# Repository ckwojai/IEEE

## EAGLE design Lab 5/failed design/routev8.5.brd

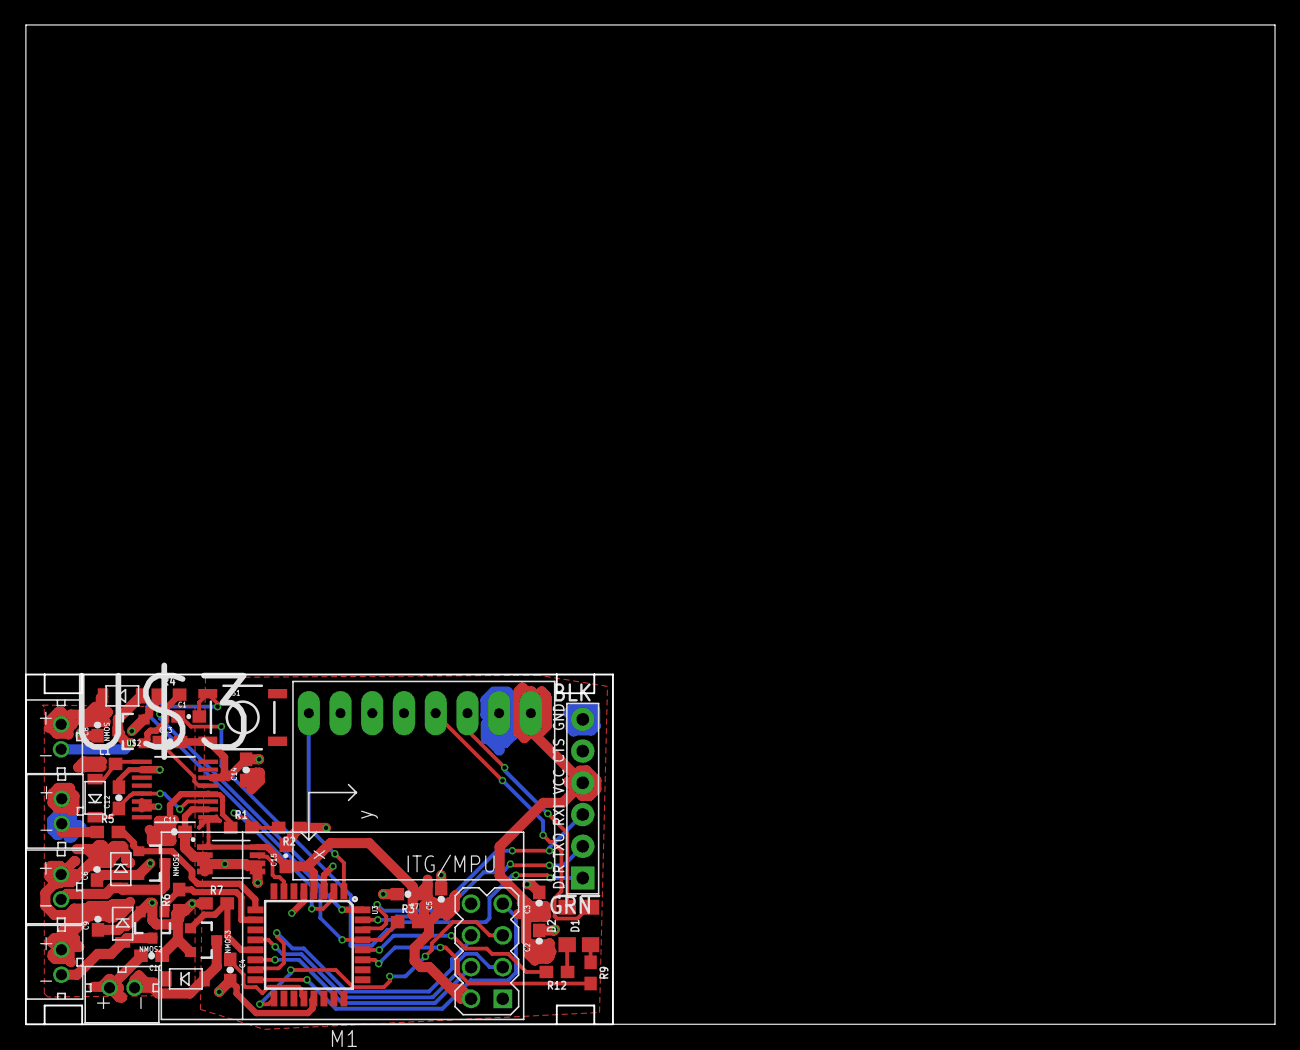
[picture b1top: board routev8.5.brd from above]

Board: 2 copper layers, 100.0 x 80.0 mm, 48 parts (0 on the bottom side), 33 nets.

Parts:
C1, C3, C4, C5, C7, C15: 100nF; 0603-CAP
C2: 10uF; 0603-CAP
C6, C8, C9, C10, C11, C12: 100uF; 0603-CAP
C13: 0.1uF; 0603-CAP
C14: 4.7uF; 0603-CAP
D1, D2: Yellow; LED-1206
DIODE, DIODE1, DIODE2, DIODE3, DIODE4: DB2W40300L; MINI2-F3-B
J2: FTDI_DEVICE; FTDI_DEVICE_SIDE
L1: 10uH; 0603
M1: WIRELESS-NRF24L01
MOTOR, MOTOR1, MOTOR2, MOTOR3: JST_CONNECTOR_FEMALE
NMOS, NMOS1, NMOS2, NMOS3: N-CHANNEL-MOSFET-IRLML6244TRPBF; SOT23-3
R1, R2: 2.2k; 0603
R3, R4, R5, R6, R7: 10k; 0603
R9, R12: 1k; 0603
S1: SWITCH-MOMENTARY-2SMD; TACTILE-SWITCH-SMD
U2: GY-521MPU6050; GY-521
U3: ATMEGA328P_TQFP; TQFP32-08
U$1: JST_CONNECTOR_FEMALE
U$2: MAX1672'MAX1672'; 21-0055H_16
U$3: LTC6930CMS8-8.19LTC6930CMS8-8.19; SOP65P490X110-8N

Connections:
BATTERY+: C6.2, C8.2, C9.2, C10.2, C11.1, DIODE.NEG, DIODE1.NEG, DIODE2.NEG, DIODE3.NEG, L1.1, MOTOR.+, MOTOR1.+, MOTOR2.+, MOTOR3.+, R1.1, U$1.+, U$2.12
FTDI-RX: J2.P$3, U3.30
FTDI-TX: J2.P$2, U3.31
GND: C2.2, C3.2, C4.2, C5.2, C6.1, C7.2, C8.1, C9.1, C10.1, C11.2, C12.2, C13.2, C14.2, C15.2, J2.P$6, M1.1, NMOS.2, NMOS1.2, NMOS2.2, NMOS3.2, R2.1, R4.1, R5.1, R6.1, R7.1, S1.3, U2.GND, U3.3, U3.5, U3.21, U$1.-, U$2.2, U$2.6, U$2.7, U$2.10, U$2.14, U$3.2, U$3.3, U$3.4, U$3.5, U$3.6
IMU-INT: U2.INT, U3.1
IMU-SCL: D2.C, U2.SCL
IMU-SDA: D1.C, U2.SDA
MEASURE_PIN: R1.2, R2.2, U3.2
MOTOR1: NMOS.1, R4.2, U3.32
MOTOR2: NMOS1.1, R5.2, U3.9
MOTOR3: NMOS2.1, R6.2, U3.10
MOTOR4: NMOS3.1, R7.2, U3.13
unnamed: DIODE4.POS, L1.2, U$2.1
unnamed: C4.1, U3.20
unnamed: D1.A, R9.1
unnamed: DIODE1.POS, MOTOR1.-, NMOS1.3
unnamed: DIODE2.POS, MOTOR2.-, NMOS2.3
unnamed: DIODE.POS, MOTOR.-, NMOS.3
unnamed: DIODE3.POS, MOTOR3.-, NMOS3.3
unnamed: R9.2, U3.27
unnamed: D2.A, R12.1
unnamed: R12.2, U3.28
unnamed: C1.1, J2.P$1
OSC1: U3.7, U$3.7
RESET: C1.2, R3.1, S1.1, U3.29
RF-CE: M1.3, U3.12
RF-CSN: M1.4, U3.14
RF-MISO: M1.7, U3.16
RF-MOSI: M1.6, U3.15
RF-SCK: M1.5, U3.17
VCC: C2.1, C3.1, C5.1, C7.1, C14.1, C15.1, J2.P$4, M1.2, R3.2, U2.VCC, U3.4, U3.18, U$2.9, U$3.1, U$3.8
VR-PS: C12.1, DIODE4.NEG, U$2.5, U$2.11
VR-REF: C13.1, U$2.13

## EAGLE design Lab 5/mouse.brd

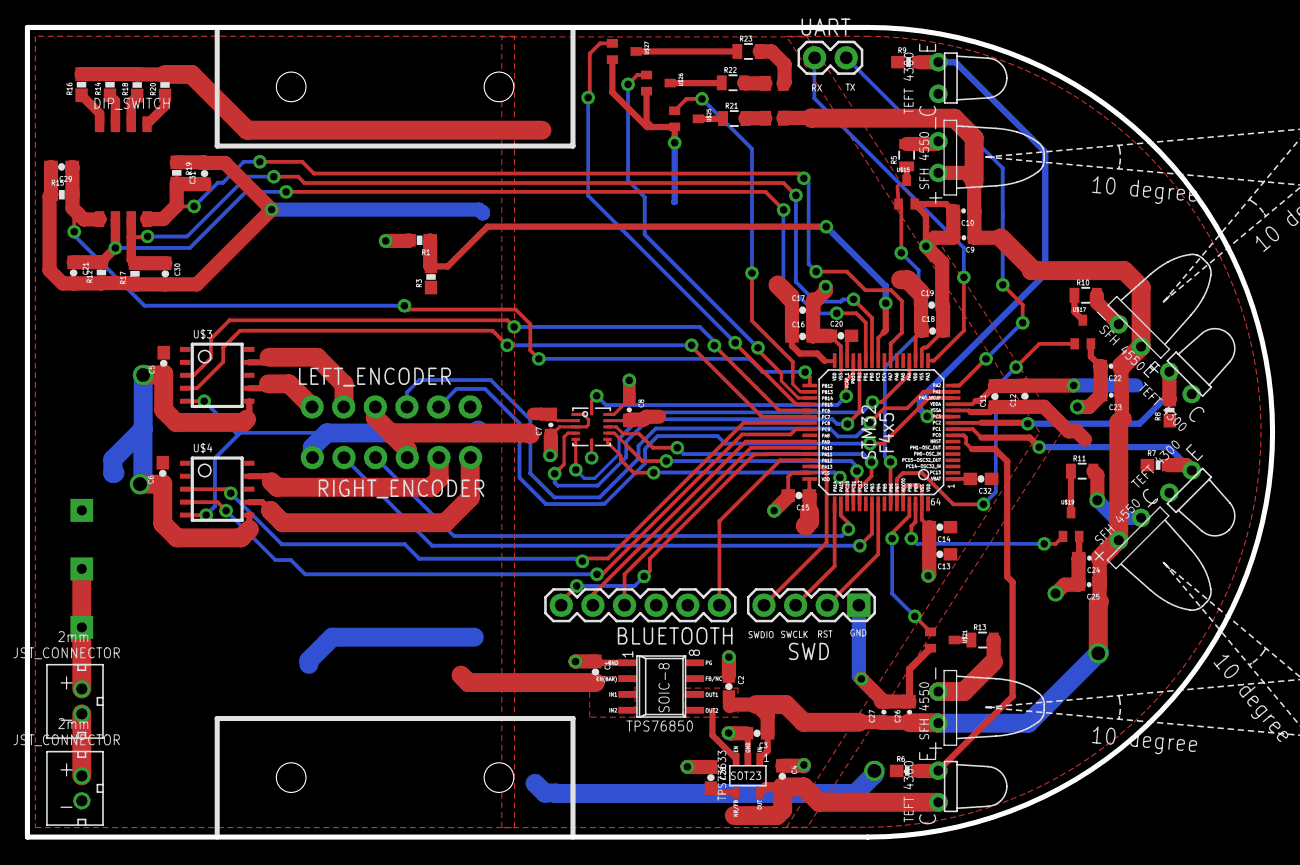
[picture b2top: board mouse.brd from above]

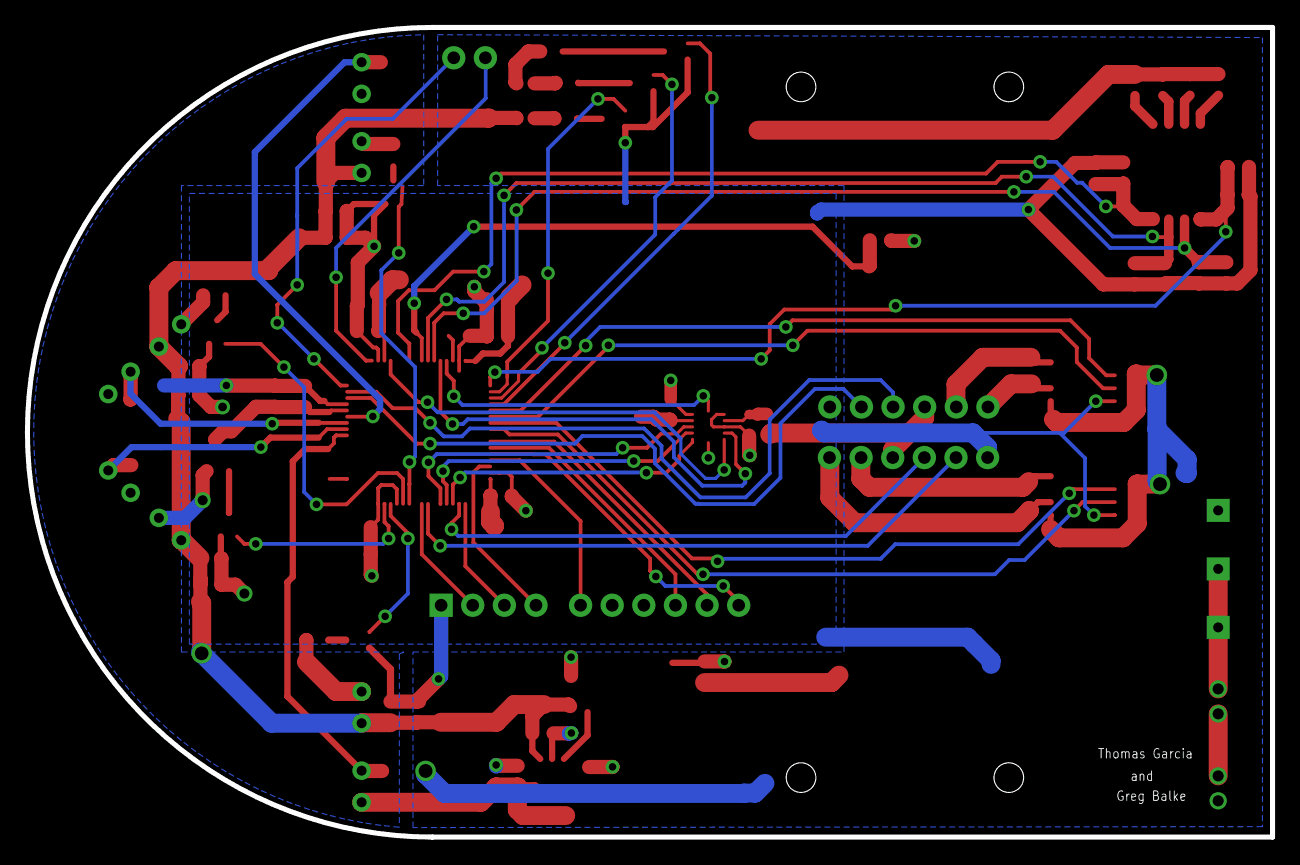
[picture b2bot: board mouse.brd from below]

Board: 2 copper layers, 100.0 x 65.0 mm, 94 parts (3 on the bottom side), 80 nets.

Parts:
BAT1, BAT2: JST_CONNECTOR_FEMALE
BLUETOOTH: 1X06
C1, C3, C7, C8, C9, C11, C13, C14, C15, C16, C17, C18, C21, C22, C24, C26, C29, C30, C31, C32: 100nF; 0603-CAP
C2, C4: 10uF; 0603-CAP
C5, C6, C12: 1uF; 0603-CAP
C10, C19, C20, C23, C25, C27: 4.7uF; 0603-CAP
C28: 10nF; 0603-CAP
DIP_SWITCH: 218_4LPSTR
LEFT_ENCODER: 1X06_NO_SILK
R1: 33k; 0603-RES
R3: 51k; 0603-RES
R5, R10, R11, R13: 36; 0805
R6, R7, R8, R9: 1.8k; 0603-RES
R12, R15, R17, R19: 10k; 0603-RES
R14, R16, R18, R20: 360; 0603-RES
R21, R22: 82; 0805
R23: 150; 0805
RIGHT_ENCODER: 1X06_NO_SILK
SWD: 1X04
U$1, U$2, U$9, U$13, U$14, U$29, U$30, U$31, U$32, U$33: SPLITTER
U$3, U$4: LB1930MCSMD; LB1930MC
U$5: XZMECBDDG45S; 4-PLCC
U$6: BMG160
U$7, U$16, U$18, U$34: EMITTER
U$8, U$10, U$11, U$12: RECEIVER
U$15, U$17, U$19, U$21, U$25, U$26, U$27: DMG1012UW
U$22: TPS76850(SOIC-8)
U$23: TPS73633(SOT-23)
U$24: STM32F411RE_LQFP64
U$28: 500SSP1S2M2QEA
UART: 1X02

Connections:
5V: C2.2, C3.1, C9.1, C10.1, C22.1, C23.1, C24.1, C25.1, C26.1, C27.1, U$5.VCC, U$7.+, U$16.+, U$18.+, U$22.OUT1, U$22.OUT2, U$23.EN, U$23.IN, U$34.+
AGND: C11.1, C12.1, R6.1, R7.1, R8.1, R9.1, U$9.1, U$24.VSSA
BAT: C1.2, C5.2, C6.2, R3.1, U$3.1, U$4.1, U$22.EN(BAR), U$22.IN1, U$22.IN2, U$28.1
BAT_DIVIDER: R1.1, R3.2, U$24.PC5
BLUE_GATE: U$24.PB13, U$25.GATE
BRX: BLUETOOTH.4, U$24.PA10
BTX: BLUETOOTH.5, U$24.PA9
BUTTON1: C29.1, DIP_SWITCH.OUT1, R15.2, U$24.PB12
BUTTON2: C21.1, DIP_SWITCH.OUT2, R12.2, U$24.PB1
BUTTON3: C30.1, DIP_SWITCH.OUT3, R17.2, U$24.PB0
BUTTON4: C31.1, DIP_SWITCH.OUT4, R19.2, U$24.PA7
CTS: BLUETOOTH.6, U$24.PA11
DGND: BLUETOOTH.3, C7.1, C8.1, C9.2, C10.2, C13.2, C14.2, C15.2, C16.2, C17.2, C18.2, C19.2, C20.1, C21.2, C22.2, C23.2, C24.2, C25.2, C26.2, C27.2, C29.2, C30.2, C31.2, LEFT_ENCODER.6, R12.1, R15.1, R17.1, R19.1, RIGHT_ENCODER.6, SWD.1, U$2.1, U$3.5, U$4.5, U$6.P$1, U$6.P$3, U$6.P$6, U$6.P$11, U$15.SOURCE, U$17.SOURCE, U$19.SOURCE, U$21.SOURCE, U$24.BOOT0, U$24.VSS_0, U$24.VSS_1, U$24.VSS_2, U$24.VSS_3, U$25.SOURCE, U$26.SOURCE, U$27.SOURCE
FRONT_LEFT_EMITTER: U$17.GATE, U$24.PB7
FRONT_LEFT_RECEIVER: R8.2, U$11.E, U$24.PC2
FRONT_RIGHT_EMITTER: U$19.GATE, U$24.PB9
FRONT_RIGHT_RECEIVER: R7.2, U$10.E, U$24.PC1
GND: BAT1.-, C1.1, C2.1, C3.2, C4.1, C28.1, R1.2, U$1.2, U$2.2, U$9.2, U$22.GND, U$23.GND
GREEN_GATE: U$24.PB14, U$26.GATE
GYRO_INT1: U$6.P$4, U$24.PB2
GYRO_INT2: U$6.P$12, U$24.PB10
LEFT_A: LEFT_ENCODER.4, U$24.PA1
LEFT_B: LEFT_ENCODER.5, U$24.PA0_WKUP
LEFT_BWD: U$3.3, U$24.PC6
LEFT_EMITTER: U$15.GATE, U$24.PB6
LEFT_FWD: U$3.4, U$24.PC7
LEFT_RECEIVER: R9.2, U$12.E, U$24.PC3
MGND: C5.1, C6.1, U$1.1, U$3.10, U$4.10
MISO: U$6.P$8, U$24.PC11
MOSI: U$6.P$9, U$24.PC12
unnamed: BAT1.+, BAT2.-
unnamed: RIGHT_ENCODER.2, U$4.7
unnamed: RIGHT_ENCODER.1, U$4.9
unnamed: LEFT_ENCODER.2, U$3.7
unnamed: LEFT_ENCODER.1, U$3.9
unnamed: R5.2, U$34.-
unnamed: BAT2.+, U$28.2, U$28.3
unnamed: C20.2, U$24.VCAP_1
unnamed: R5.1, U$15.DRAIN
unnamed: R10.2, U$7.-
unnamed: R10.1, U$17.DRAIN
unnamed: R11.2, U$16.-
unnamed: R21.2, U$5.BLUE
unnamed: R11.1, U$19.DRAIN
unnamed: R13.2, U$18.-
unnamed: R13.1, U$21.DRAIN
unnamed: C28.2, U$23.NR/FB
unnamed: C4.2, U$13.2, U$14.2, U$23.OUT
unnamed: C32.2, U$24.VBAT
unnamed: DIP_SWITCH.IN2, R14.1
unnamed: DIP_SWITCH.IN1, R16.1
unnamed: R22.2, U$5.GREEN
unnamed: DIP_SWITCH.IN3, R18.1
unnamed: R23.2, U$5.RED
unnamed: DIP_SWITCH.IN4, R20.1
unnamed: R22.1, U$26.DRAIN
unnamed: R21.1, U$25.DRAIN
unnamed: R23.1, U$27.DRAIN
unnamed: C8.2, U$6.P$10, U$32.2
unnamed: C7.2, U$6.P$2, U$31.2
RED_GATE: U$24.PB15, U$27.GATE
RIGHT_A: RIGHT_ENCODER.4, U$24.PA15
RIGHT_B: RIGHT_ENCODER.5, U$24.PB3
RIGHT_BWD: U$4.3, U$24.PC8
RIGHT_EMITTER: U$21.GATE, U$24.PB8
RIGHT_FWD: U$4.4, U$24.PC9
RIGHT_RECEIVER: R6.2, U$8.E, U$24.PC0
RST: SWD.2, U$24.PB4
RTS: BLUETOOTH.1, U$24.PA12
RX: U$24.PA3, UART.1
SCK: U$6.P$7, U$24.PC10
SS: U$6.P$5, U$24.PA4
SWCLK: SWD.3, U$24.PA14
SWDIO: SWD.4, U$24.PA13
TX: U$24.PA2, UART.2
VDD: BLUETOOTH.2, C13.1, C14.1, C32.1, LEFT_ENCODER.3, R14.2, R16.2, R18.2, R20.2, RIGHT_ENCODER.3, U$13.1, U$24.VDD_3, U$29.2, U$30.2, U$31.1, U$32.1, U$33.1
VDD15: C15.1, U$24.VDD_2, U$33.2
VDDA: C11.2, C12.2, U$8.C, U$10.C, U$11.C, U$12.C, U$14.1, U$24.VDDA
VDD_0: C18.1, C19.1, U$24.VDD_0, U$30.1
VDD_1: C16.1, C17.1, U$24.VDD_1, U$29.1

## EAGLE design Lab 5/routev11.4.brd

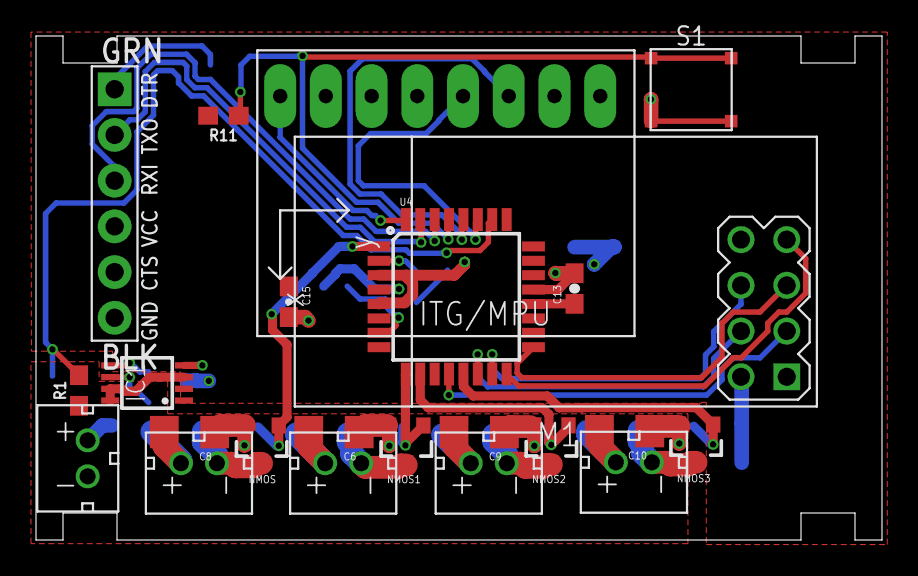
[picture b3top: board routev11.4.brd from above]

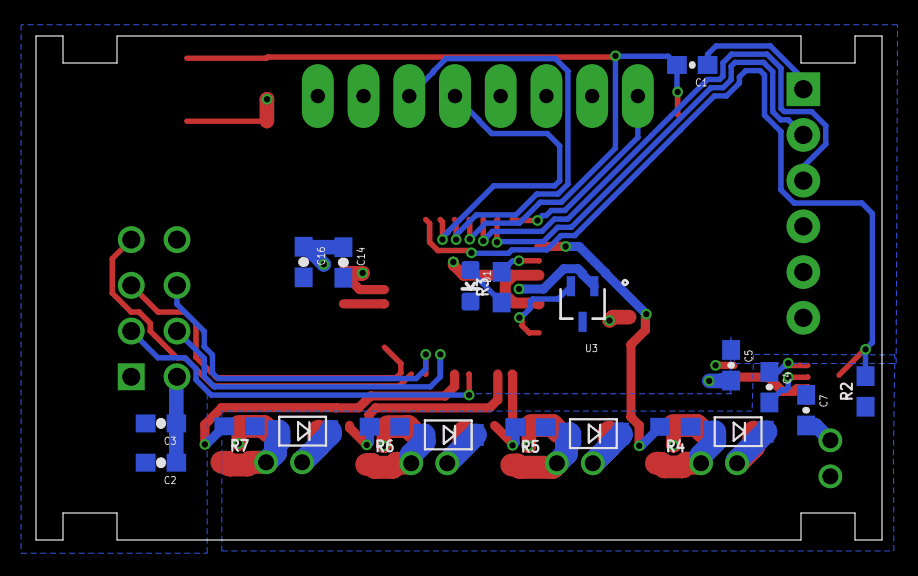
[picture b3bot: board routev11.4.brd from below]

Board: 2 copper layers, 47.0 x 28.0 mm, 43 parts (20 on the bottom side), 30 nets.

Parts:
C1, C3, C13, C14, C15, C16: 100nF; 0603-CAP
C2, C5, C7: 10uF; 0603-CAP
C4: 1uF; 0603-CAP
C6, C8, C9, C10: 100uF; 1206
D1: BLUE; LED-0603
DIODE, DIODE1, DIODE2, DIODE3: DB2W40300L; MINI2-F3-B
IC1: MCP1253-ADJ; MSOP8
J1: FTDI_DEVICE; FTDI_DEVICE_SIDE
M1: WIRELESS-NRF24L01
MOTOR1, MOTOR2, MOTOR3, MOTOR4: JST_CONNECTOR_FEMALE
NMOS, NMOS1, NMOS2, NMOS3: N-CHANNEL-MOSFET-IRLML6244TRPBF; SOT23-3
R1, R2, R3: 2.2k; 0603
R4, R5, R6, R7, R11: 10k; 0603
S1: TL3315NF100Q
U2: GY-521MPU6050; GY-521
U3: MAX7375AXR805-T; 21-0075D
U4: ATMEGA328P_TQFP; TQFP32-08
U$1: JST_CONNECTOR_FEMALE

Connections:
BATTERY+: C6.2, C7.2, C8.2, C9.2, C10.2, DIODE.NEG, DIODE1.NEG, DIODE2.NEG, DIODE3.NEG, IC1.3, IC1.7, IC1.8, MOTOR1.+, MOTOR2.+, MOTOR3.+, MOTOR4.+, R1.1, U$1.+
FTDI-RX: J1.P$3, U4.30
FTDI-TX: J1.P$2, U4.31
GND: C2.2, C3.2, C5.1, C6.1, C7.1, C8.1, C9.1, C10.1, C13.2, C14.2, C15.2, C16.2, D1.C, IC1.4, J1.P$6, M1.1, NMOS.2, NMOS1.2, NMOS2.2, NMOS3.2, R2.1, R4.1, R5.1, R6.1, R7.1, S1.3, S1.4, U2.GND, U3.3, U4.3, U4.5, U4.21, U$1.-
IMU-INT: U2.INT, U4.32
IMU-SCL: U2.SCL, U4.28
IMU-SDA: U2.SDA, U4.27
MEASURE_PIN: R1.2, R2.2, U4.26
MOTOR1: NMOS.1, R4.2, U4.1
MOTOR2: NMOS1.1, R5.2, U4.9
MOTOR3: NMOS2.1, R6.2, U4.10
MOTOR4: NMOS3.1, R7.2, U4.13
unnamed: R3.2, U4.2
unnamed: C1.1, J1.P$1
unnamed: DIODE1.POS, MOTOR2.-, NMOS1.3
unnamed: DIODE2.POS, MOTOR3.-, NMOS2.3
unnamed: DIODE.POS, MOTOR1.-, NMOS.3
unnamed: DIODE3.POS, MOTOR4.-, NMOS3.3
unnamed: C4.1, IC1.5
unnamed: C4.2, IC1.6
unnamed: D1.A, R3.1
unnamed: C13.1, U4.20
OSC1: U3.2, U4.7
RESET: C1.2, R11.1, S1.1, S1.2, U4.29
RF-CE: M1.3, U4.12
RF-CSN: M1.4, U4.14
RF-MISO: M1.7, U4.16
RF-MOSI: M1.6, U4.15
RF-SCK: M1.5, U4.17
VCC: C2.1, C3.1, C5.2, C14.1, C15.1, C16.1, IC1.2, J1.P$4, M1.2, R11.2, U2.VCC, U3.1, U4.4, U4.6, U4.18

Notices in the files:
parts and their libraries:
SparkFun-Capacitors: Licensing: Creative Commons ShareAlike 4.0 International - https://creativecommons.org/licenses/by-sa/4.0
SparkFun: Licensing: CC v3.0 Share-Alike You are welcome to use this library for commercial purposes.
